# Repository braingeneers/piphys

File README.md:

# piphys

Update: The latest manuscript about Piphys has been published in IOP Journal of Neural Engineering!

Peer-reviewed journal article: 

[Light-weight electrophysiology hardware and software platform for cloud-based neural recording experiments](https://iopscience.iop.org/article/10.1088/1741-2552/ac310a/pdf)

The original [preprint](https://www.biorxiv.org/content/10.1101/2021.05.18.444685v2) can still be accessed on bioRxiv.

--------
## Overview

Piphys is an inexpensive open source neurophysiological recording platform based on Raspberry Pi. It is easily accessed and controlled via a standard web interface through Internet of Things (IoT) protocols. 

Piphys modules can be used in a fleet to enable long-term observations of neural development, organization, and activity at scale. 

## Design Files

### Hardware
- Raspberry Pi expansion circuit board for and Intan RHD2000 bioamplifier chip.
- Electrode adapter circuit board for Axion CytoView MEA Plate.

Source files, documentation, and files for manufacturing each circuit board are in [`./Hardware`](https://github.com/braingeneers/piphys/tree/main/Hardware).

#### Electrode mapping

There are 64 electrodes in a well B2 of the Axion CytoView MEA Plate. The electrode adapter circuit board allows 32 of the 64 electrodes to be recorded by Piphys. The green dots are the recorded channels, labeled with their channel number in the data file sampling sequence.

### Mechanical
CAD files in for the electrode plate holder are in [`./Mechanical/AxionPlateHolder`](https://github.com/braingeneers/piphys/tree/main/Mechanical/AxionPlateHolder).

Assembly Order:
```
AxionPlateHolder_CNC_ClampTop_Aluminum
---------------------------------------
[Axion CytoView MEA Plate]
---------------------------------------
AxionPlateHolder_CNC_ClampBottom_Plastic
AxionPlateHolder_CNC_ClampBottom_Aluminum
```

### Software
Software to enable voltage sampling and user interaction, with accompanying documentation are in [`./Software`](https://github.com/braingeneers/piphys/tree/main/Software).

See [`braingeneerpy`](https://github.com/braingeneers/braingeneerspy) Python package for IoT communication library.

### Test Data
System validation data with sine wave are available at the Piphys [`Google Drive folder`](https://drive.google.com/drive/folders/1S5Uj3old0Q09hUaioH9NGgg6K85ICtAz?usp=sharing).

----
### UC Santa Cruz (UCSC) Noncommercial License

Acceptance

In order to get any license under these terms, you must agree to them as both strict obligations and conditions to all your licenses.

Copyright License

The licensor grants you a copyright license for the repository to do everything you might do with the repository that would otherwise infringe the licensor's copyright in it for any permitted purpose.

Notices

You must ensure that anyone who gets a copy of any part of the repository from you also gets a copy of these terms, as well as the following copyright notice:

This repository is Copyright © 2021. The Regents of the University of California (“Regents”). All Rights Reserved.

Noncommercial Purposes

Any noncommercial purpose is a permitted purpose.

Commercial Purposes

Contact Innovation Transfer, UC Santa Cruz, techno@ucsc.edu , https://officeofresearch.ucsc.edu/iatc/ , for any commercial purpose.

Personal Uses

Personal use for research, experiment, and testing for the benefit of public knowledge, personal study, private entertainment, hobby projects, amateur pursuits, or religious observance, without any anticipated commercial application, is use for a permitted purpose.

Noncommercial Organizations

Use by any charitable organization, educational institution, public research organization, public safety or health organization, environmental protection organization, or government institution is use for a permitted purpose regardless of the source of funding or obligations resulting from the funding.

Fair Use

You may have "fair use" rights for the repository under the law. These terms do not limit them.

No Other Rights

These terms do not allow you to sublicense or transfer any of your licenses to anyone else, or prevent the licensor from granting licenses to anyone else.  These terms do not imply any other licenses.

Patent Defense

If you make any written claim that the repository infringes or contributes to infringement of any patent, all your licenses for the repository granted under these terms end immediately. If your company makes such a claim, all your licenses end immediately for work on behalf of your company.

Violations

The first time you are notified in writing that you have violated any of these terms, or done anything with the repository not covered by your licenses, your licenses can nonetheless continue if you come into full compliance with these terms, and take practical steps to correct past violations, within 32 days of receiving notice.  Otherwise, all your licenses end immediately.

No Liability

As far as the law allows, the repository comes as is, without any warranty or condition, and the licensor will not be liable to you for any damages arising out of these terms or the use or nature of the repository, under any kind of legal claim.

Definitions

The "licensor" is Regents, and the "repository" is the repository the licensor makes available under these terms.

"You" refers to the individual or entity agreeing to these terms.

"Your company" is any legal entity, sole proprietorship, or other kind of organization that you work for, plus all organizations that have control over, are under the control of, or are under common control with that organization.  

"Control" means ownership of substantially all the assets of an entity, or the power to direct its management and policies by vote, contract, or otherwise.  Control can be direct or indirect.

"Your licenses" are all the licenses granted to you for the repository under these terms.

"Use" means anything you do with the repository requiring one of your licenses.

© 2021 Braingeneers

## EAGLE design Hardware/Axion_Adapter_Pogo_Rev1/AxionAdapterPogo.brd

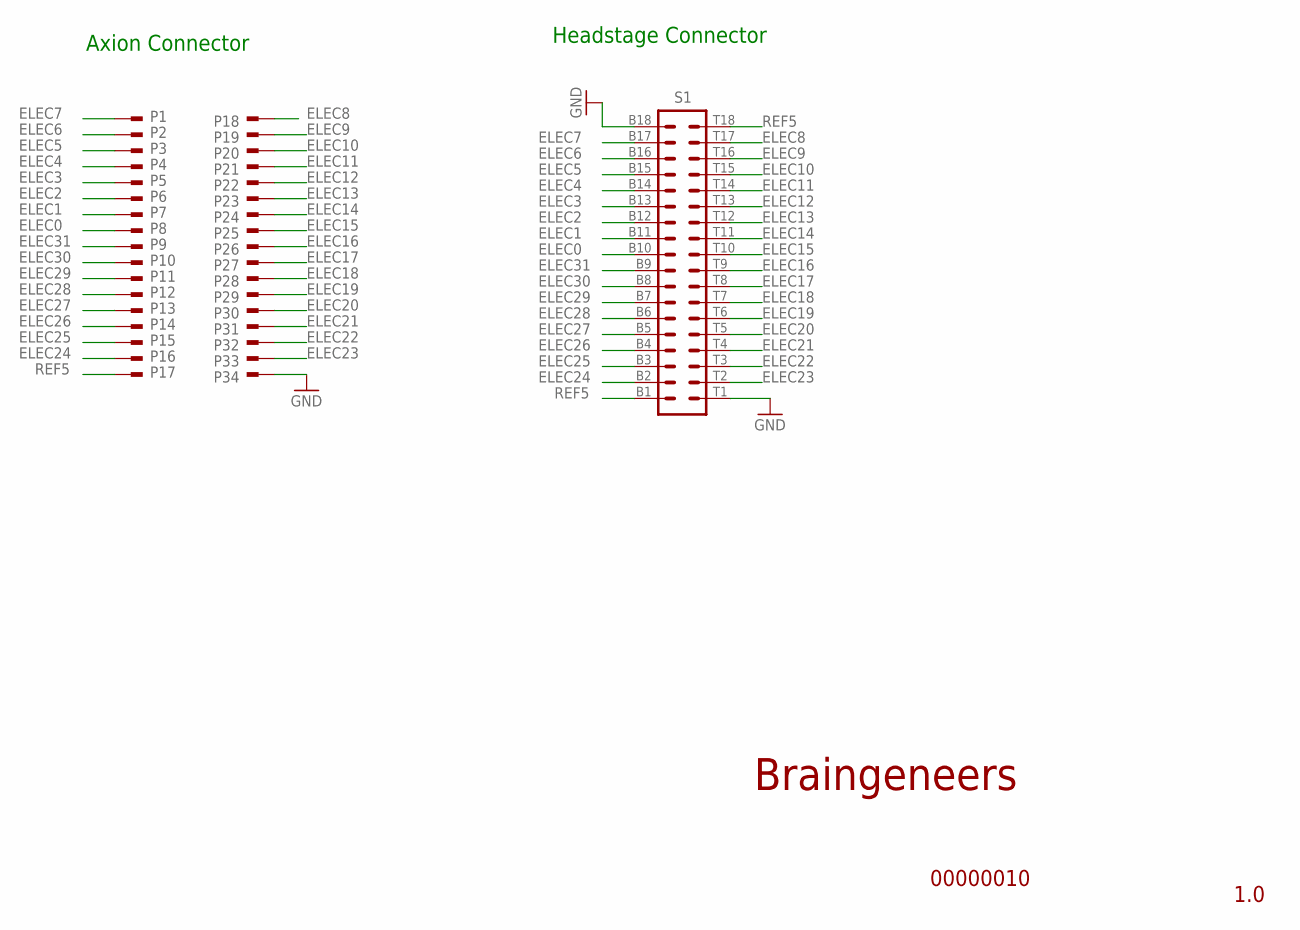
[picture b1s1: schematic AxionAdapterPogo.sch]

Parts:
P1, P2, P3, P4, P5, P6, P7, P8, P9, P10, P11, P12, P13, P14, P15, P16, P17, P18, P19, P20, P21, P22, P23, P24, P25, P26, P27, P28, P29, P30, P31, P32, P33, P34: MILL-MAX_POGO_0985-0-15-20-71-14-11-0
S1: OMNETICS_A79024

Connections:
ELEC0: P8.P$1, S1.B10
ELEC1: P7.P$1, S1.B11
ELEC2: P6.P$1, S1.B12
ELEC3: P5.P$1, S1.B13
ELEC4: P4.P$1, S1.B14
ELEC5: P3.P$1, S1.B15
ELEC6: P2.P$1, S1.B16
ELEC7: P1.P$1, S1.B17
ELEC8: P18.P$1, S1.T17
ELEC9: P19.P$1, S1.T16
ELEC10: P20.P$1, S1.T15
ELEC11: P21.P$1, S1.T14
ELEC12: P22.P$1, S1.T13
ELEC13: P23.P$1, S1.T12
ELEC14: P24.P$1, S1.T11
ELEC15: P25.P$1, S1.T10
ELEC16: P26.P$1, S1.T9
ELEC17: P27.P$1, S1.T8
ELEC18: P28.P$1, S1.T7
ELEC19: P29.P$1, S1.T6
ELEC20: P30.P$1, S1.T5
ELEC21: P31.P$1, S1.T4
ELEC22: P32.P$1, S1.T3
ELEC23: P33.P$1, S1.T2
ELEC24: P16.P$1, S1.B2
ELEC25: P15.P$1, S1.B3
ELEC26: P14.P$1, S1.B4
ELEC27: P13.P$1, S1.B5
ELEC28: P12.P$1, S1.B6
ELEC29: P11.P$1, S1.B7
ELEC30: P10.P$1, S1.B8
ELEC31: P9.P$1, S1.B9
GND: P34.P$1, S1.B18, S1.T1
REF5: P17.P$1, S1.B1, S1.T18

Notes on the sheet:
1.0
00000010
Braingeneers
Headstage Connector
Axion Connector

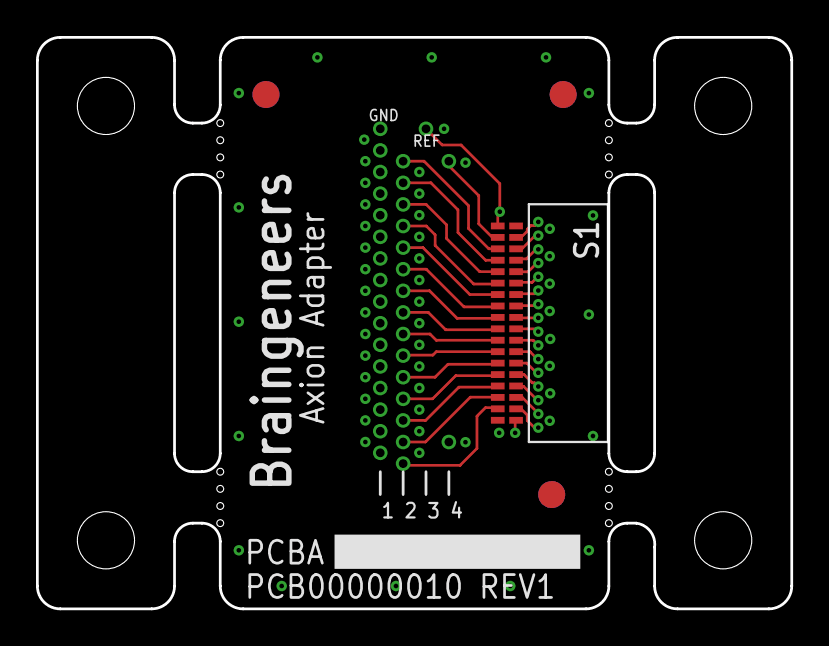
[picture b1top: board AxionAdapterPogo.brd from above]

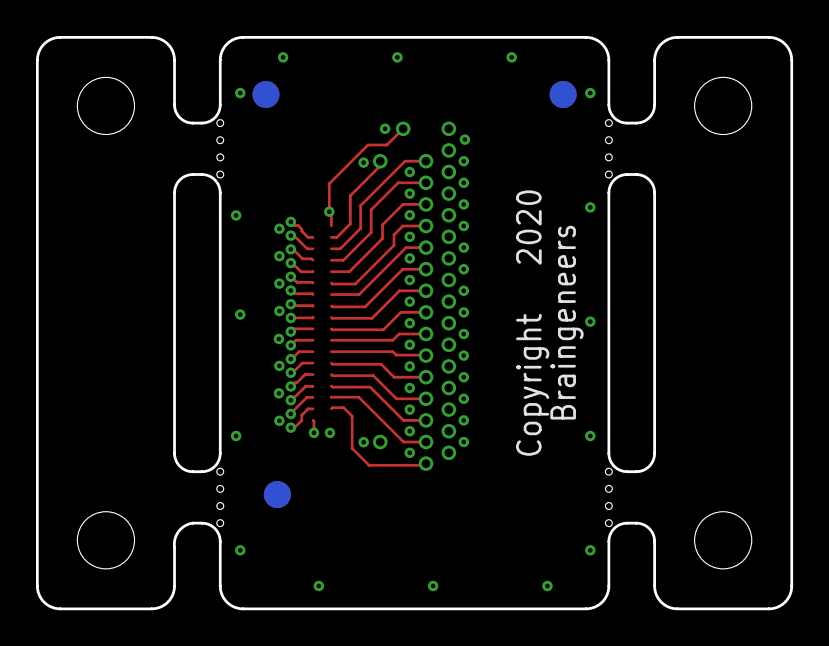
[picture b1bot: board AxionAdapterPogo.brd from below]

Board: 4 copper layers, 41.9 x 31.8 mm, 48 parts (38 on the bottom side), 34 nets.

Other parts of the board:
DRILEGEND: DRILEGEND
U$1, U$2, U$35, U$49, U$50, U$73: FIDUCIAL_G15
U$7: NASS_LOGO_LG
U$31: ROHS_LG
U$52: A5L-LOC
U$70: NO_TRASH_LG
U$72: STATIC_LG
U$84: COMPYRIGHT_MED

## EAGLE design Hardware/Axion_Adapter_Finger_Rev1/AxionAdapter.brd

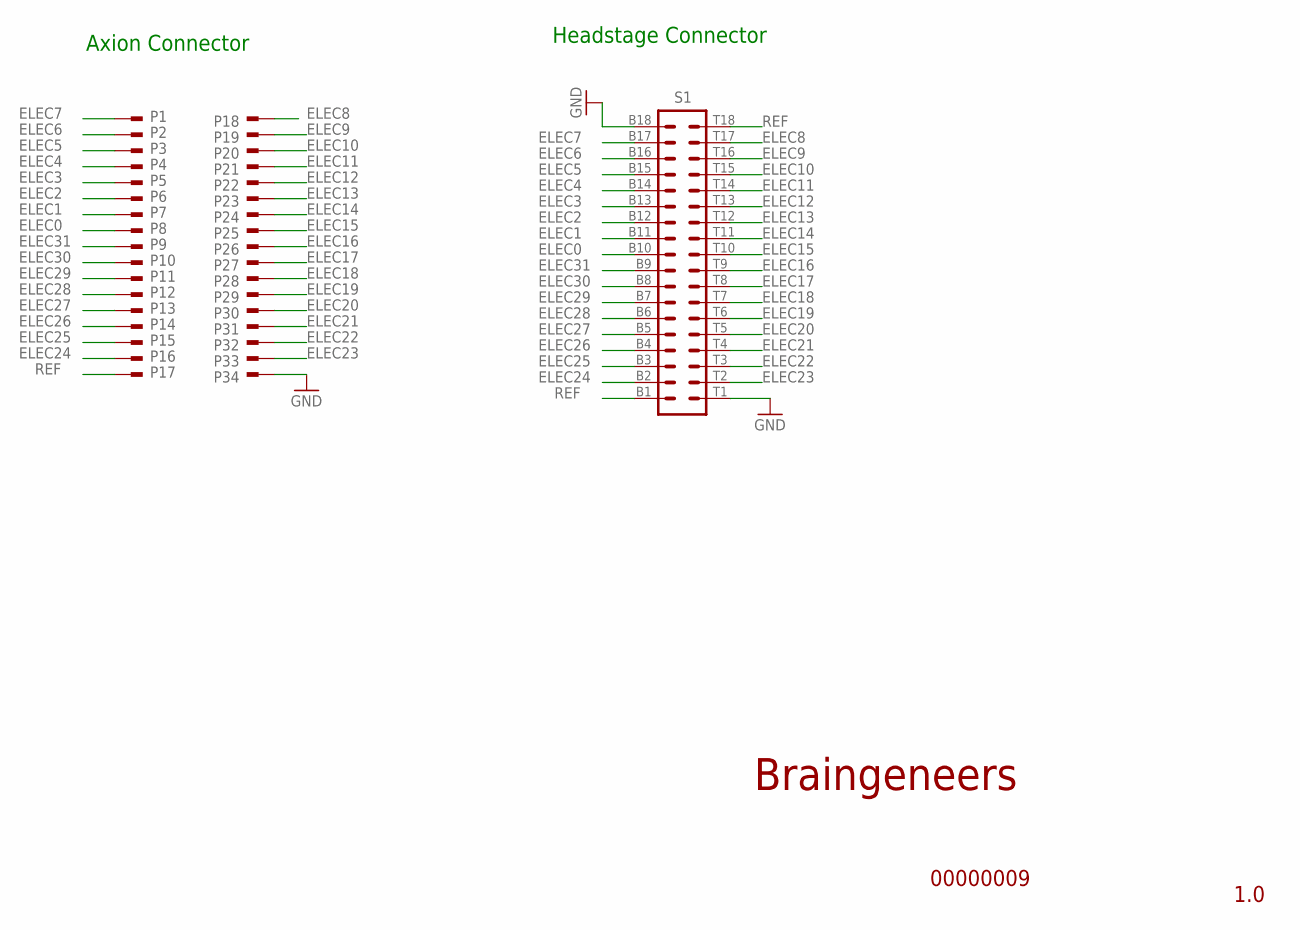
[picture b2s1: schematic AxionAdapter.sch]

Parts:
P1, P2, P3, P4, P5, P6, P7, P8, P9, P10, P11, P12, P13, P14, P15, P16, P17, P18, P19, P20, P21, P22, P23, P24, P25, P26, P27, P28, P29, P30, P31, P32, P33, P34: 2336713-2_TE
S1: OMNETICS_A79024

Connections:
ELEC0: P8.P$1, P8.P$2, S1.B10
ELEC1: P7.P$1, P7.P$2, S1.B11
ELEC2: P6.P$1, P6.P$2, S1.B12
ELEC3: P5.P$1, P5.P$2, S1.B13
ELEC4: P4.P$1, P4.P$2, S1.B14
ELEC5: P3.P$1, P3.P$2, S1.B15
ELEC6: P2.P$1, P2.P$2, S1.B16
ELEC7: P1.P$1, P1.P$2, S1.B17
ELEC8: P18.P$1, P18.P$2, S1.T17
ELEC9: P19.P$1, P19.P$2, S1.T16
ELEC10: P20.P$1, P20.P$2, S1.T15
ELEC11: P21.P$1, P21.P$2, S1.T14
ELEC12: P22.P$1, P22.P$2, S1.T13
ELEC13: P23.P$1, P23.P$2, S1.T12
ELEC14: P24.P$1, P24.P$2, S1.T11
ELEC15: P25.P$1, P25.P$2, S1.T10
ELEC16: P26.P$1, P26.P$2, S1.T9
ELEC17: P27.P$1, P27.P$2, S1.T8
ELEC18: P28.P$1, P28.P$2, S1.T7
ELEC19: P29.P$1, P29.P$2, S1.T6
ELEC20: P30.P$1, P30.P$2, S1.T5
ELEC21: P31.P$1, P31.P$2, S1.T4
ELEC22: P32.P$1, P32.P$2, S1.T3
ELEC23: P33.P$1, P33.P$2, S1.T2
ELEC24: P16.P$1, P16.P$2, S1.B2
ELEC25: P15.P$1, P15.P$2, S1.B3
ELEC26: P14.P$1, P14.P$2, S1.B4
ELEC27: P13.P$1, P13.P$2, S1.B5
ELEC28: P12.P$1, P12.P$2, S1.B6
ELEC29: P11.P$1, P11.P$2, S1.B7
ELEC30: P10.P$1, P10.P$2, S1.B8
ELEC31: P9.P$1, P9.P$2, S1.B9
GND: P34.P$1, P34.P$2, S1.B18, S1.T1
REF: P17.P$1, P17.P$2, S1.B1, S1.T18

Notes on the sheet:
1.0
00000009
Braingeneers
Headstage Connector
Axion Connector

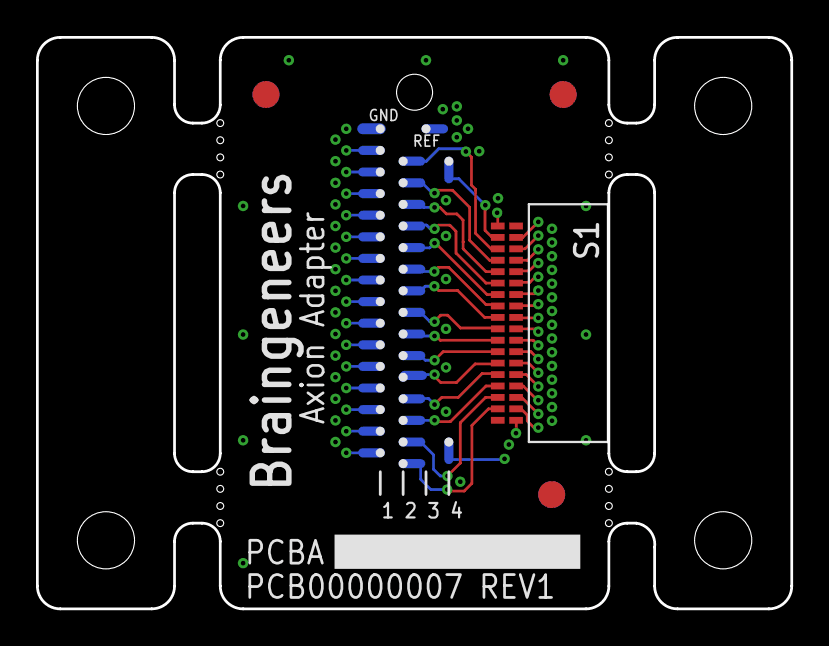
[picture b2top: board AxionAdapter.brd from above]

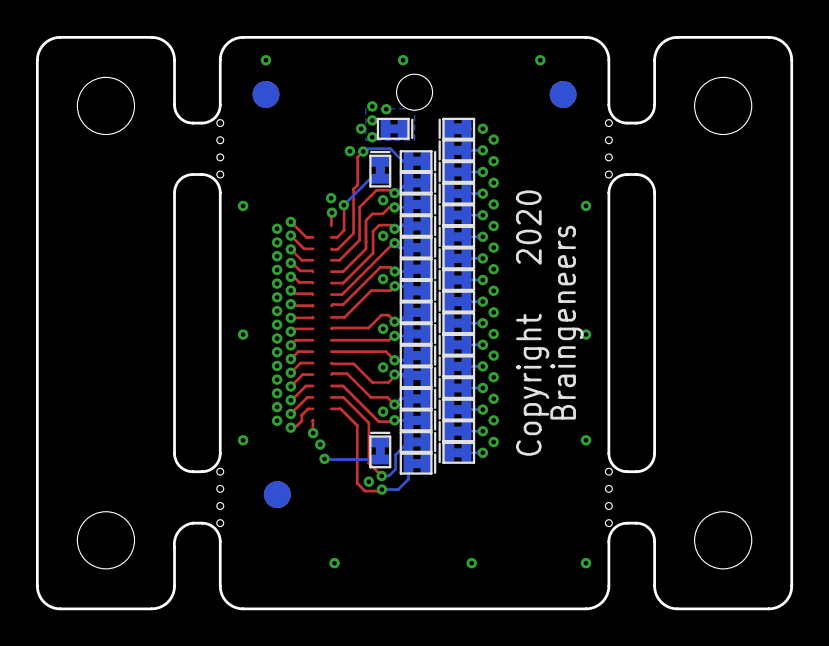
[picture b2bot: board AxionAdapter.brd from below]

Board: 4 copper layers, 41.9 x 31.8 mm, 48 parts (38 on the bottom side), 34 nets.

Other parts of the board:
DRILEGEND: DRILEGEND
U$1, U$2, U$35, U$49, U$50, U$73: FIDUCIAL_G15
U$7: NASS_LOGO_LG
U$31: ROHS_LG
U$52: A5L-LOC
U$70: NO_TRASH_LG
U$72: STATIC_LG
U$84: COMPYRIGHT_MED

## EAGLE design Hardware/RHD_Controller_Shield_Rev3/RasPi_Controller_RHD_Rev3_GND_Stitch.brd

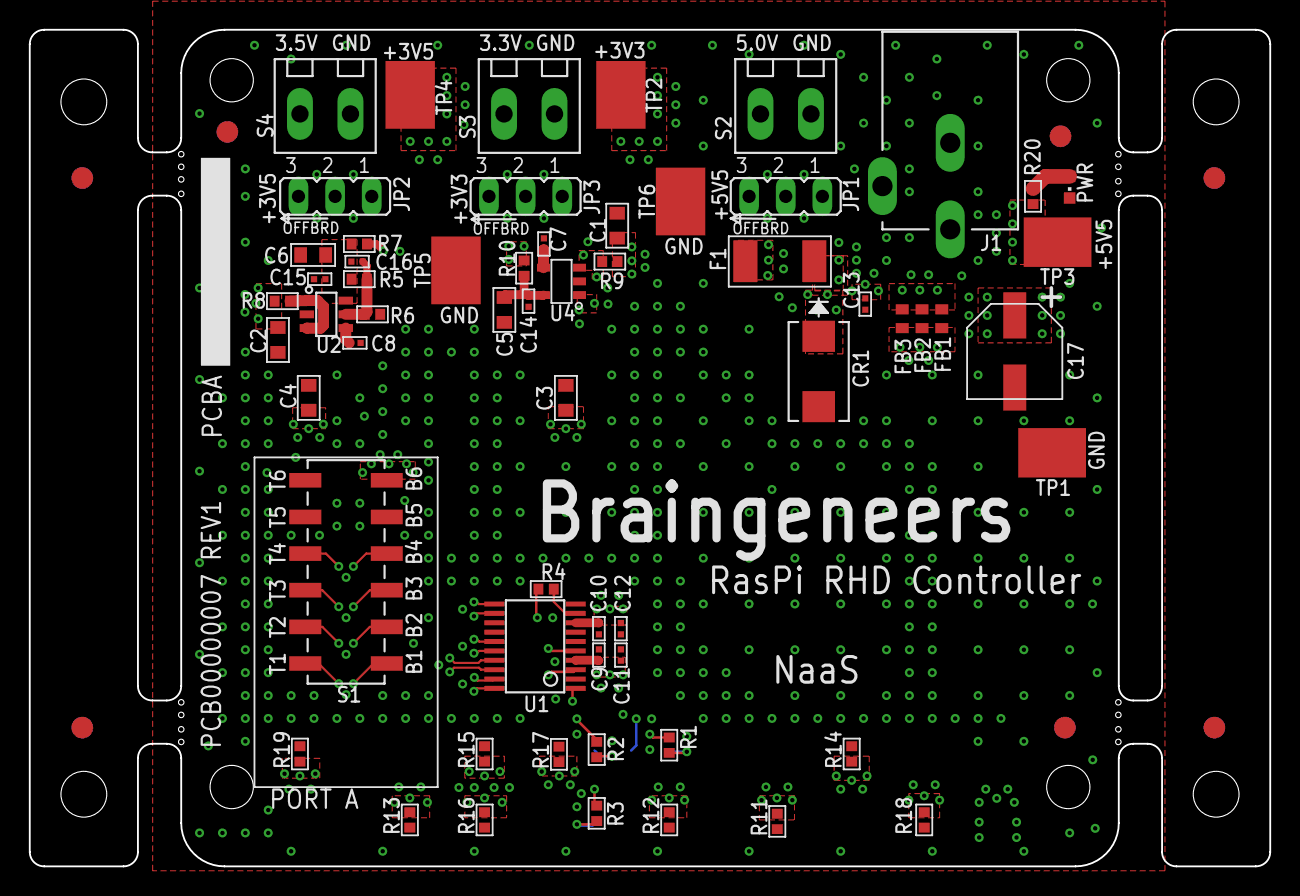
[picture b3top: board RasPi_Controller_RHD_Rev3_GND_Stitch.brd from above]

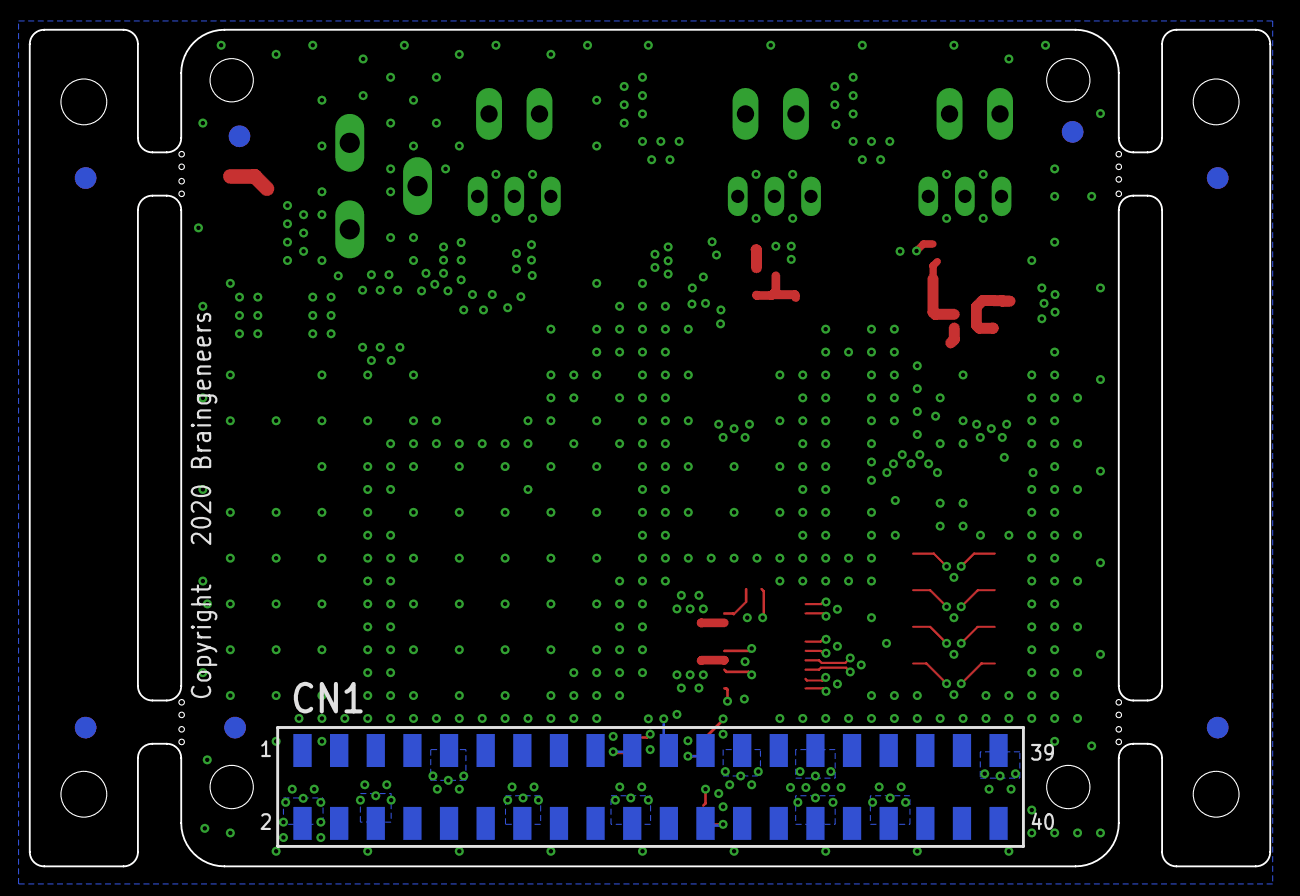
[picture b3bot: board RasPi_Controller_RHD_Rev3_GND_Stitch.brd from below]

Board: 4 copper layers, 86.0 x 58.0 mm, 83 parts (7 on the bottom side), 45 nets.

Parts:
C1, C2: 1.0u; 0603
C3, C4, C5, C6: 22u; 0603
C7, C8, C9, C10: 10n; 0201
C11, C12, C13, C14, C15: 100n; 0201
C16: 15p; 0201
C17: 100u; EEE-HAE101XAP
CN1: ADA3708SMT_PI_HEADER_FEMALE; SAMTEC-HLE-120-02-X-DV
CR1: SMBJ5.0A; DIODE_DO214AA
DRILEGEND: DRILEGEND
F1: MF-MSMF250/X; MF-MSMF250/16X-2
FB1, FB2, FB3: BLM15HB121SN1; 0402
J1: DC_POWER_JACK-PJ-102AH; PJ-102AH
JP1, JP2, JP3: JP2
PWR: CHIPLED_0603
R1, R2, R3, R4: 22.1; 0402
R5: 56.0K; 0402
R6: 30.1K; 0402
R7, R8, R9, R10, R11, R12, R13, R14, R15, R16, R17, R18, R19: 0; 0402
R20: 1K; 0402
S1: RHD2000-CABLE-DAQ-SIDEINTAN_SMT_SPI_CABLE_ADAPTER; INTAN_SMT_RHD_SPI_CABLE_ADAPTER
S2: TERMINAL_BLOCK_2-3.5MM-5V; TERMINAL_BLOCK_3.5MM_2_5V
S3: TERMINAL_BLOCK_2-3.5MM-3.3V; TERMINAL_BLOCK_3.5MM_2_3.3V
S4: TERMINAL_BLOCK_2-3.5MM-3.5V; TERMINAL_BLOCK_3.5MM_2_3.5V
TP1, TP2, TP3, TP4, TP5, TP6: 5016
U1: SN65LVDT41; TSSOP-20
U2: TPS79301; SOT-23-6
U4: TPS79333; TSOT-23-5
U$1, U$32, U$34, U$35, U$36, U$48, U$49, U$50, U$51, U$67, U$68, U$69, U$73, U$75: FIDUCIAL_G15
U$7: NASS_LOGO_LG
U$31: ROHS_LG
U$33: LOGO_BRAINGENEERS_H_12MM
U$52: A5L-LOC
U$70: NO_TRASH_LG
U$72: STATIC_LG
U$84: COMPYRIGHT_MED

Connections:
!CS!: R3.2, U1.1
!CS!_N: S1.T1, U1.19
!CS!_P: S1.B1, U1.20
+3V3: C3.1, C9.1, C10.1, C11.1, C12.1, JP3.2, TP2.P$1, U1.4, U1.8
+3V3_REG: C5.1, C14.1, R10.2, U4.5
+3V5: C4.1, JP2.2, S1.B6, TP4.P$1
+5V: C1.1, C2.1, C17.1, CN1.2, FB1.2, FB2.2, FB3.2, R8.2, R9.2, R20.1, TP3.P$1
+5V_JACK: J1.1, JP1.1
GND: C1.2, C2.2, C3.2, C4.2, C5.2, C6.2, C7.2, C8.2, C9.2, C10.2, C11.2, C12.2, C13.2, C14.2, C15.2, C17.2, CR1.2, J1.2, J1.3, PWR.C, R6.2, R11.1, R12.1, R13.1, R14.2, R15.2, R16.1, R17.2, R18.1, R19.2, S1.T6, S2.1, S3.1, S4.1, TP1.P$1, TP5.P$1, TP6.P$1, U1.2, U1.6, U1.10, U2.2, U4.2
MISO: CN1.21, R4.2
MISO_N: S1.T4, U1.11
MISO_P: S1.B4, U1.12
MOSI: R1.2, U1.5
MOSI_N: S1.T3, U1.15
MOSI_P: S1.B3, U1.16
unnamed: C13.1, CR1.1, F1.P$2, FB1.1, FB2.1, FB3.1
unnamed: CN1.6, R18.2
unnamed: CN1.30, R16.2
unnamed: C8.1, U2.4
unnamed: PWR.A, R20.2
unnamed: CN1.25, R17.1
unnamed: CN1.29, R15.1
unnamed: CN1.9, R14.1
unnamed: CN1.14, R11.2
unnamed: CN1.20, R12.2
unnamed: CN1.34, R13.2
unnamed: JP1.3, S2.2
unnamed: C16.2, R5.2, R6.1, U2.5
unnamed: C7.1, U4.4
unnamed: R9.1, U4.1, U4.3
unnamed: R8.1, U2.1, U2.3
unnamed: F1.P$1, JP1.2
unnamed: JP3.3, S3.2
unnamed: JP2.3, S4.2
unnamed: JP2.1, R7.1
unnamed: JP3.1, R10.1
unnamed: CN1.23, R2.1
unnamed: CN1.24, R3.1
unnamed: R4.1, U1.9
unnamed: CN1.39, R19.1
unnamed: CN1.19, R1.1
SCLK: R2.2, U1.3
SCLK_N: S1.T2, U1.17
SCLK_P: S1.B2, U1.18
U2_OUT: C6.1, C15.1, C16.1, R5.1, R7.2, U2.6

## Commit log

2021-05-09 Hardware designs added
2021-05-10 added software
2021-08-03 Added mechanical, hardware, and image files
2021-08-03 Fixed links
2021-08-03 Fixed side image
2021-08-03 Added dashboard photo
2021-08-03 Cleaned up Axion Adapter revisions
2021-08-03 Added electrode mapping description
2021-08-03 Created readme.md
2021-10-11 Modified Redis queue
2022-12-20 Updated Non-commercial License to README.md
2023-05-25 Added pogo pin Axion adapter design
2024-02-20 Update README.md
    fixed typo

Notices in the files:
Hardware/Axion_Adapter_Finger_Rev1/AxionAdapter.brd:
Copyright 2020
Hardware/RHD_Controller_Shield_Rev3/RasPi_Controller_RHD_Rev3_GND_Stitch.brd:
Copyright 2020 Braingeneers
parts and their libraries:
dicons: Copyright (C) 2004, Bob Starr (rtzaudio@mindspring.com)
